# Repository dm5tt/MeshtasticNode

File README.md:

## What is this thing?

This is a Heltec HT-CT62 based Meshtastic Router which can be integrated into a IP68 protected case.

Combined with a solar panel this device can be placed in remote areas to cover a wide range.

For power management a TI BQ24074 is being used which offers pseudo-MPPT and load switching (= battery being deactivated if the sun offers us enough energy to power the device alone).

Voltages can be measured via power divider to GPIO0 (VBUS) or GPIO1 (LiPo)

## But the power consumption of the ESP32 sucks!

Yes and no.

In this setup we don't plan to use BT or Wifi which are famous for their power consumption on this microcontroller.

With the Meshtastic power saving features enabled it will mostly spend its time in light- or even deep-sleep. It automatically wakes up by a pin-triggered interrupt signal.

Even with only a 1000mAh LiPo it will survive for days. Without (!) solar.

I soon will make some power traces with the Nordic Power Analyzer kit.

## Do I have to modify the Software?

Only some smaller pin mapping changes are required. Maybe I'll upstream this in a few weeks.

```
diff --git a/variants/heltec_esp32c3/pins_arduino.h b/variants/heltec_esp32c3/pins_arduino.h
index a717a370..b8ebc09c 100644
--- a/variants/heltec_esp32c3/pins_arduino.h
+++ b/variants/heltec_esp32c3/pins_arduino.h
@@ -6,8 +6,8 @@
 static const uint8_t TX = 21;
 static const uint8_t RX = 20;
 
-static const uint8_t SDA = 1;
-static const uint8_t SCL = 0;
+static const uint8_t SDA = 18;
+static const uint8_t SCL = 19;
 
 static const uint8_t SS = 8;
 static const uint8_t MOSI = 7;
diff --git a/variants/heltec_esp32c3/variant.h b/variants/heltec_esp32c3/variant.h
index 360d9bf1..4f66476d 100644
--- a/variants/heltec_esp32c3/variant.h
+++ b/variants/heltec_esp32c3/variant.h
@@ -1,16 +1,11 @@
-#define BUTTON_PIN 9

-#define LED_PIN 2 // LED
-#define LED_INVERTED 0

 #define HAS_SCREEN 0
 #define HAS_GPS 0
 #undef GPS_RX_PIN
 #undef GPS_TX_PIN
 
+#define BATTERY_PIN 1
+#define ADC_CHANNEL ADC1_GPIO1_CHANNEL
+
 #define USE_SX1262
 #define LORA_SCK 10
 #define LORA_MISO 6
```

### Box

### Cabeling

### Flashing

## Lessons learned

Never ever use hot glue even when if the promise that it's UV resistant. It will fail and then the environment will kill all of your electronics.

Professional glue for construction work and water pools/boat seem to survive every kind of weather as long you keep it within its specs.

Using venting plugs with gore tex membrane.

## Future Changes

The solar charging IC will be replaced with    the new TI BQ25308 which will enable us to utilize solar panels from 4.5-17V without burning a single mA into heat.

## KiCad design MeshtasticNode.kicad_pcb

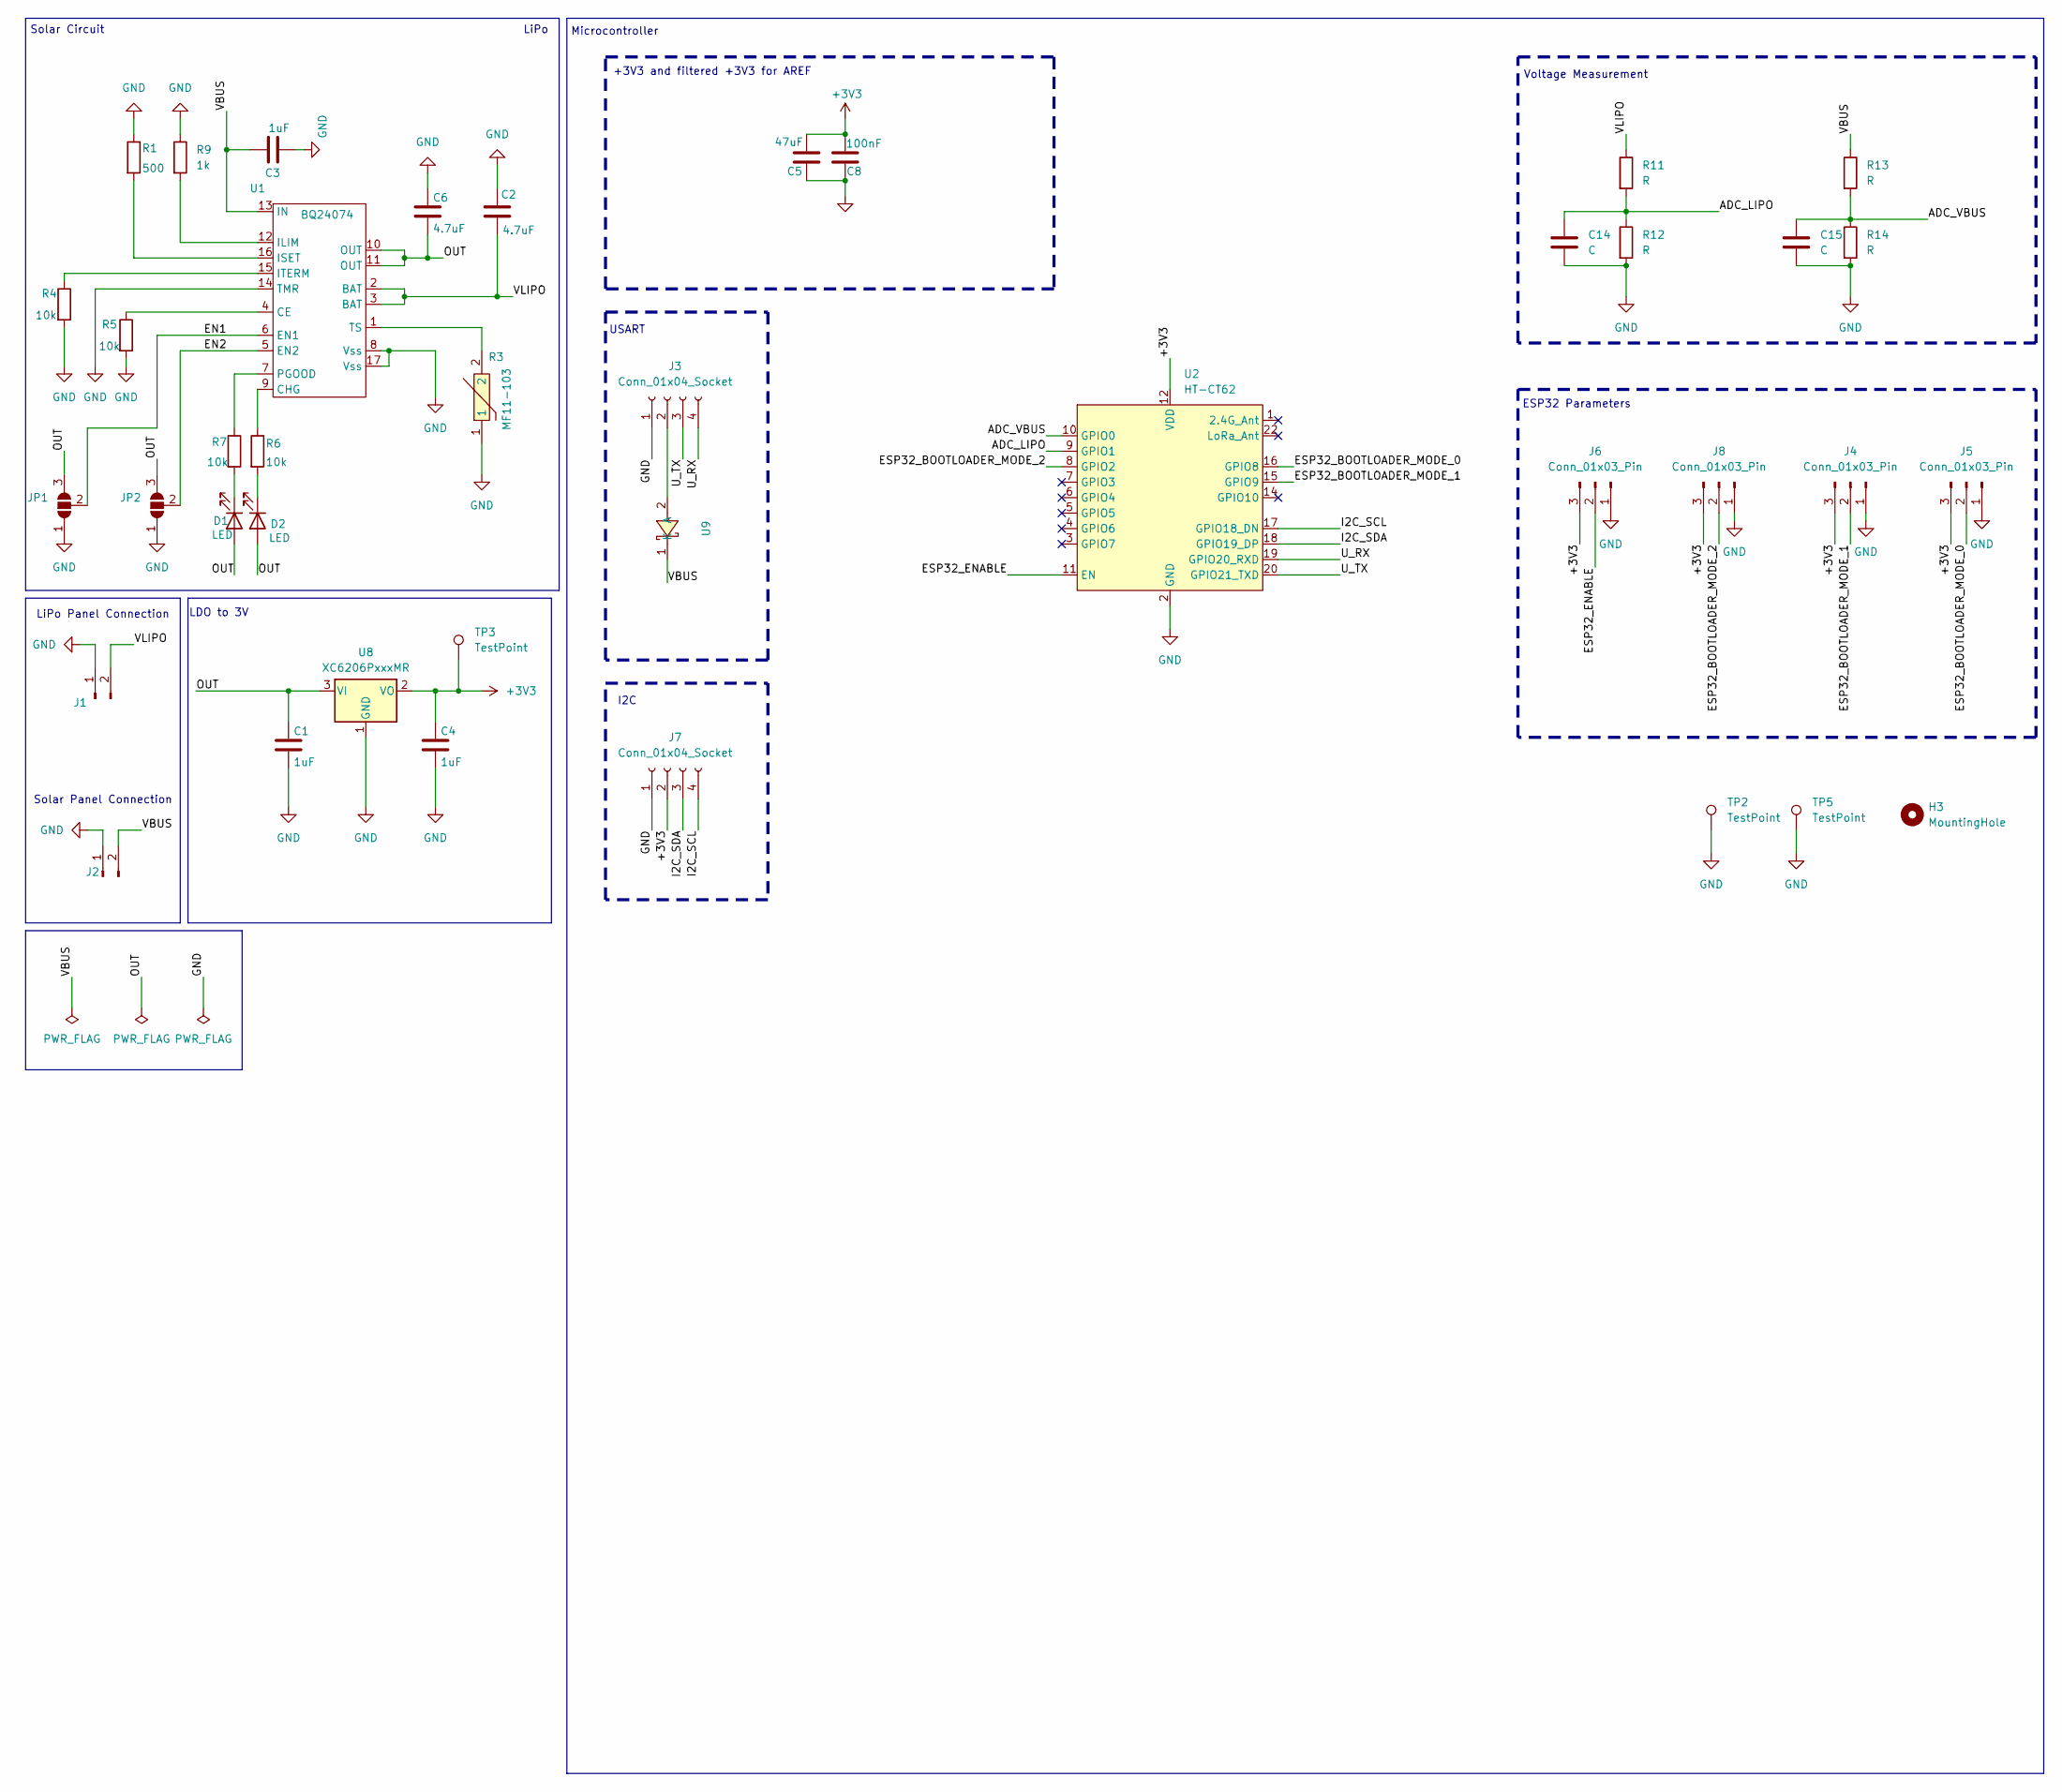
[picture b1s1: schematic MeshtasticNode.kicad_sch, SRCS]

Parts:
C1, C3, C4: 1uF; C_0805_2012Metric_Pad1.18x1.45mm_HandSolder
C2, C6: 4.7uF; C_0805_2012Metric_Pad1.18x1.45mm_HandSolder
C5: 47uF; R_1206_3216Metric_Pad1.30x1.75mm_HandSolder
C8: 100nF; C_0805_2012Metric_Pad1.18x1.45mm_HandSolder
C14, C15: C; C_0805_2012Metric_Pad1.18x1.45mm_HandSolder
D1, D2: LED; LED_0805_2012Metric_Pad1.15x1.40mm_HandSolder
H3: MountingHole; MountingHole_4.3mm_M4_DIN965
J1, J2: Conn_01x02_Socket; JST_PH_B2B-PH-K_1x02_P2.00mm_Vertical
J3, J7: Conn_01x04_Socket; JST_PH_B4B-PH-K_1x04_P2.00mm_Vertical
J4, J5, J6, J8: Conn_01x03_Pin; PinHeader_1x03_P2.54mm_Vertical
JP1, JP2: SolderJumper_3_Open; SolderJumper-3_P1.3mm_Open_RoundedPad1.0x1.5mm_NumberLabels
R1: 500; R_0805_2012Metric_Pad1.20x1.40mm_HandSolder
R3: MF11-103; RES-TH_L6.5-W4.0-P2.50-D0.5; LCSC Part C70913
R4, R5, R6, R7: 10k; R_0805_2012Metric_Pad1.20x1.40mm_HandSolder
R9: 1k; R_0805_2012Metric_Pad1.20x1.40mm_HandSolder
R11, R12, R13, R14: R; R_0805_2012Metric_Pad1.20x1.40mm_HandSolder
TP2, TP3, TP5: TestPoint; PinHeader_1x01_P2.54mm_Vertical
U1: BQ24074; VQFN-16-1EP_3x3mm_P0.5mm_EP1.68x1.68mm_ThermalVias
U2: HT-CT62; Heltec_HT-CT62
U8: XC6206PxxxMR; SOT-23-3
U9: SS26_C5350986; SMA_L4.3-W2.6-LS5.1-RD; LCSC Part C5350986

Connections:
+3V3: C4.1, C5.2, C8.2, J4.3, J5.3, J6.3, J7.2, J8.3, TP3.1, U2.12 (VDD), U8.2 (VO)
/ADC_LIPO: C14.1, R11.2, R12.1, U2.9 (GPIO1)
/ADC_VBUS: C15.1, R13.2, R14.1, U2.10 (GPIO0)
/EN1: JP1.2 (C), U1.6 (EN1)
/EN2: JP2.2 (C), U1.5 (EN2)
/ESP32_BOOTLOADER_MODE_0: J5.2, U2.16 (GPIO8)
/ESP32_BOOTLOADER_MODE_1: J4.2, U2.15 (GPIO9)
/ESP32_BOOTLOADER_MODE_2: J8.2, U2.8 (GPIO2)
/ESP32_ENABLE: J6.2, U2.11 (EN)
/I2C_SCL: J7.4, U2.17 (GPIO18_DN)
/I2C_SDA: J7.3, U2.18 (GPIO19_DP)
/OUT: C1.1, C6.2, D1.2 (A), D2.2 (A), JP1.3 (B), JP2.3 (B), U1.10 (OUT), U1.11 (OUT), U8.3 (VI)
/U_RX: J3.4, U2.19 (GPIO20_RXD)
/U_TX: J3.3, U2.20 (GPIO21_TXD)
/VBUS: C3.1, J2.2, R13.1, U1.13 (IN), U9.1 (K)
/VLIPO: C2.2, J1.2, R11.1, U1.2 (BAT), U1.3 (BAT)
GND: C1.2, C2.1, C3.2, C4.2, C5.1, C6.1, C8.1, C14.2, C15.2, J1.1, J2.1, J3.1, J4.1, J5.1, J6.1, J7.1, J8.1, JP1.1 (A), JP2.1 (A), R1.1, R3.1, R4.2, R5.2, R9.1, R12.2, R14.2, TP2.1, TP5.1, U1.8 (Vss), U1.14 (TMR), U1.17 (Vss), U2.2 (GND), U2.13 (GND), U2.21 (GND), U8.1 (GND)
unnamed: D1.1 (K), R7.2
unnamed: D2.1 (K), R6.2
unnamed: J3.2, U9.2 (A)
unnamed: R5.1, U1.4 (CE)
unnamed: R6.1, U1.9 (CHG)
unnamed: R9.2, U1.12 (ILIM)
unnamed: R1.2, U1.16 (ISET)
unnamed: R4.1, U1.15 (ITERM)
unnamed: R7.1, U1.7 (PGOOD)
unnamed: R3.2, U1.1 (TS)

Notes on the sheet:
ESP32 Parameters
Solar Circuit
Microcontroller
USART
Voltage Measurement
LiPo
LiPo Panel Connection
+3V3 and filtered +3V3 for AREF
Solar Panel Connection
LDO to 3V
I2C

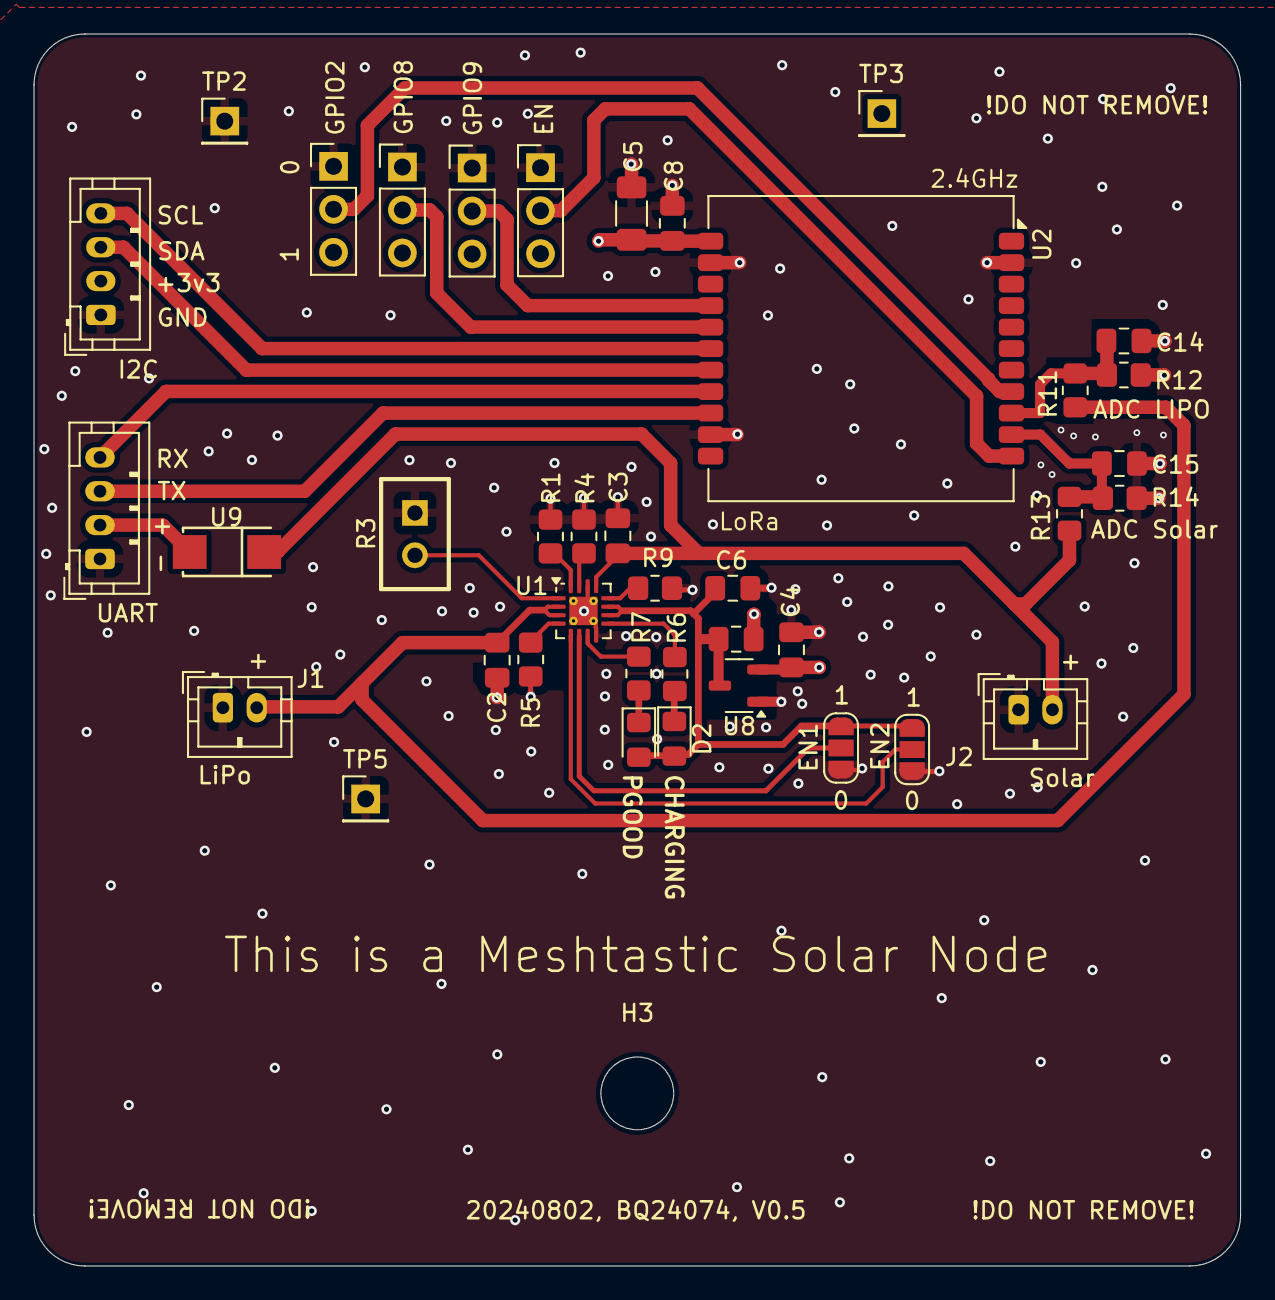
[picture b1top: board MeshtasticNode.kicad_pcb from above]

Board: 4 copper layers, 71.3 x 72.8 mm, 40 parts (0 on the bottom side), 27 nets.

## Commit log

2024-07-21 Rename Pictures
2024-07-21 Readme: fix typo
2024-07-21 Readme: add details
2024-07-21 Readme: we don't have to remove this code comments
2024-07-21 README: we don't have to touch the TXCO
2024-07-21 Increase maximum current from 500mA to 2A
2024-07-22 pcb: Make EN1 and EN2 selectable. Fixes awful bug.
2024-07-22 pcb: replace picture
2024-07-22 pcb: prepare for v0.3
2024-07-22 pcb: increase maximum current from 500mA to 2A
2024-07-22 Readme: fix typos and add details
2024-07-22 pcb: remove 90° ankle
2024-07-22 pcb: add I2C port and remove a few warnings from EN1/EN2 solder switches
2024-07-23 Readme: add some text regarding power savings with the ESP32
2024-07-23 Readme: update spelling
2024-08-02 pcb: add lost front and back groundplane, use thermal via footprint for BQ24074
2024-08-02 Add License (GPLv3)
2024-08-03 pcb: smaller non-functional cleanups of the design
2024-08-03 pcb: smaller non-functional cleanups
